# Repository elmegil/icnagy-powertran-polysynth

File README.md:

Forking a powertran polysynth project that appears to have died off before completion

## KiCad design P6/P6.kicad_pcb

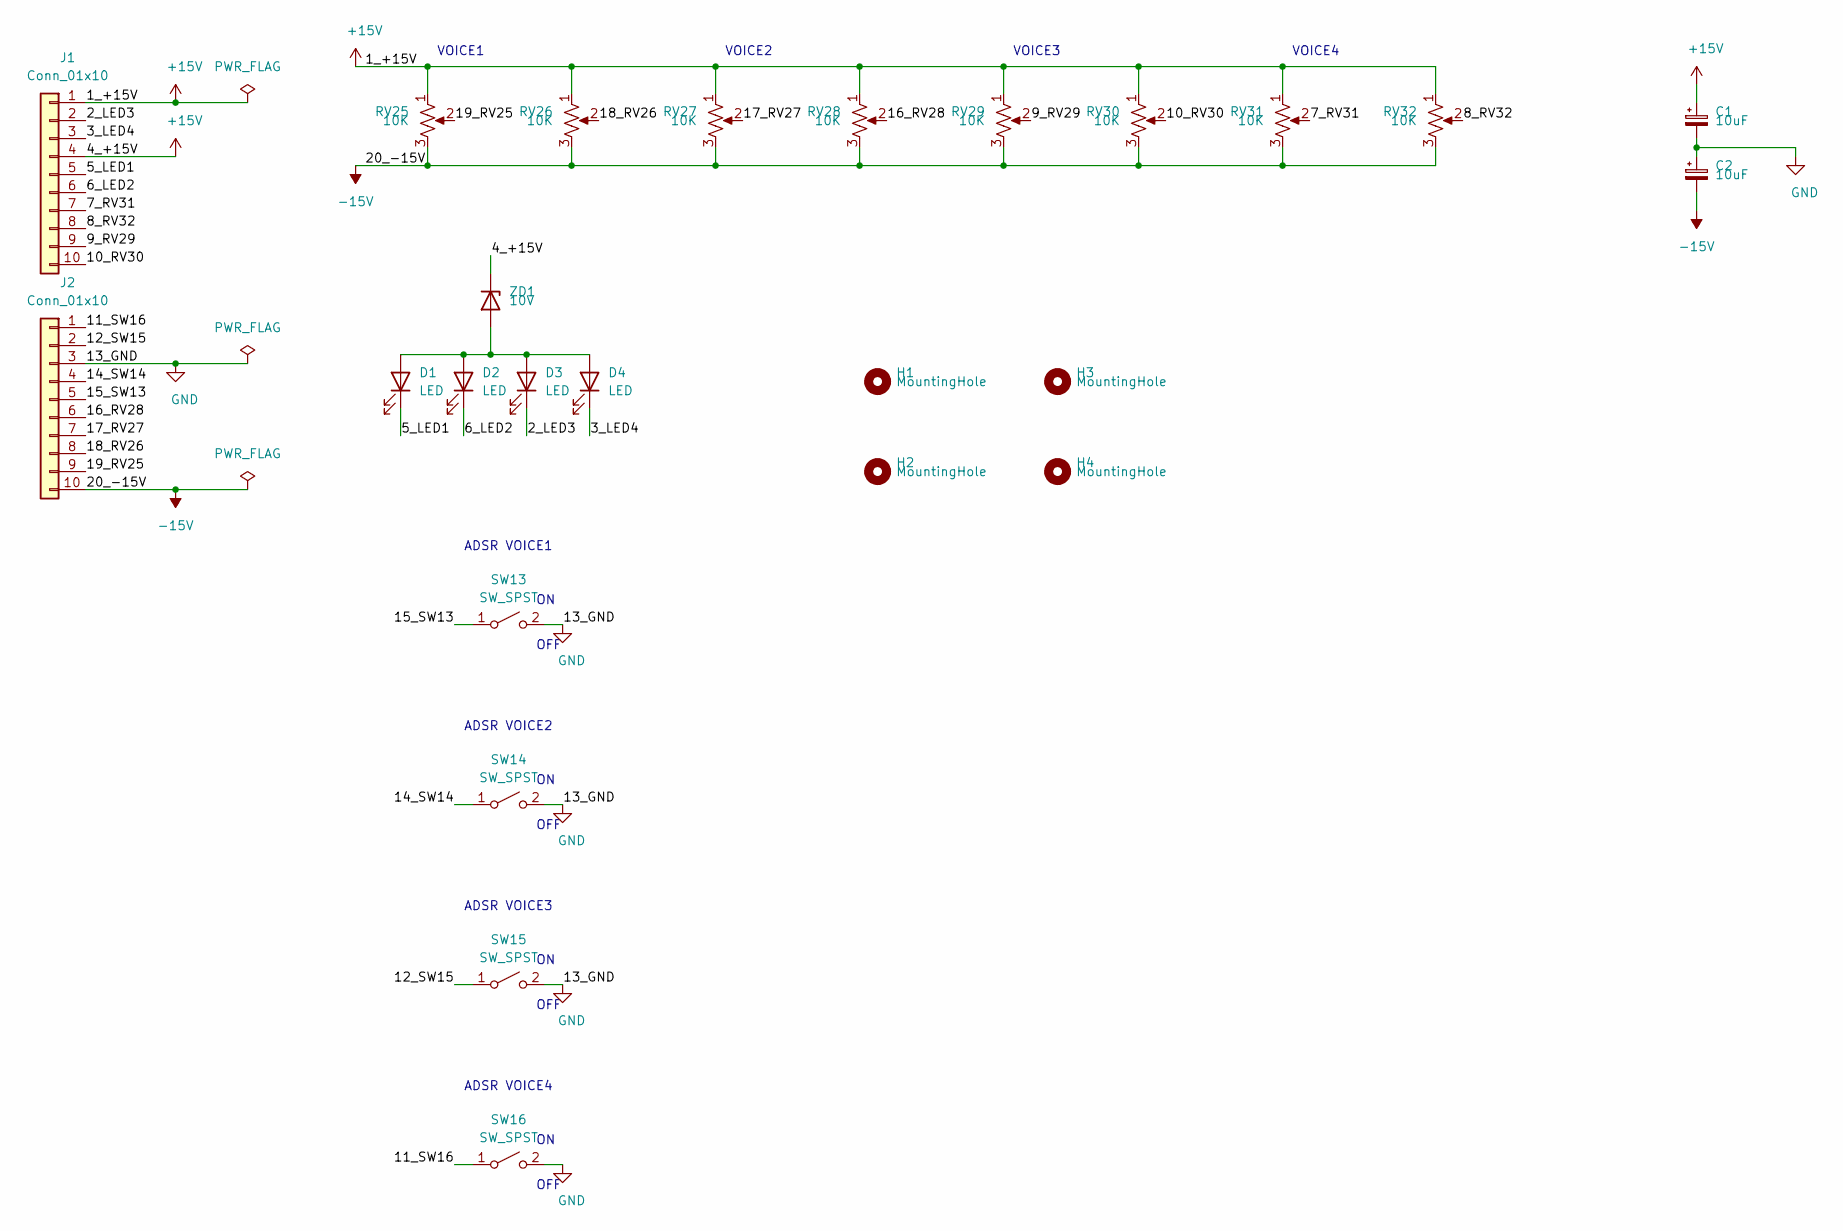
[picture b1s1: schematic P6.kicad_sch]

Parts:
C1, C2: 10uF; CP_Radial_D8.0mm_P3.50mm
D1, D2, D3, D4: LED; LED_D3.0mm
H1, H2, H3, H4: MountingHole; MountingHole_3.2mm_M3_Pad
J1, J2: Conn_01x10; PinSocket_1x10_P2.54mm_Vertical
RV25, RV26, RV27, RV28, RV29, RV30, RV31, RV32: 10K; Potentiometer_Omeg_PC16BU_Vertical
SW13, SW14, SW15, SW16: SW_SPST; SW_Slide_1P2T_CK_OS102011MS2Q
ZD1: 10V; D_A-405_P10.16mm_Horizontal

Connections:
+15V: C1.1, J1.1, J1.4, RV25.1, RV26.1, RV27.1, RV28.1, RV29.1, RV30.1, RV31.1, RV32.1, ZD1.1 (K)
-15V: C2.2, J2.10, RV25.3, RV26.3, RV27.3, RV28.3, RV29.3, RV30.3, RV31.3, RV32.3
/2_LED3: D3.1 (K), J1.2
/3_LED4: D4.1 (K), J1.3
/5_LED1: D1.1 (K), J1.5
/6_LED2: D2.1 (K), J1.6
/7_RV31: J1.7, RV31.2
/8_RV32: J1.8, RV32.2
/9_RV29: J1.9, RV29.2
/10_RV30: J1.10, RV30.2
/11_SW16: J2.1, SW16.1 (A)
/12_SW15: J2.2, SW15.1 (A)
/14_SW14: J2.4, SW14.1 (A)
/15_SW13: J2.5, SW13.1 (A)
/16_RV28: J2.6, RV28.2
/17_RV27: J2.7, RV27.2
/18_RV26: J2.8, RV26.2
/19_RV25: J2.9, RV25.2
GND: C1.2, C2.1, J2.3, SW13.2 (B), SW14.2 (B), SW15.2 (B), SW16.2 (B)
unnamed: D1.2 (A), D2.2 (A), D3.2 (A), D4.2 (A), ZD1.2 (A)

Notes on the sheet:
OFF
VOICE4
VOICE2
VOICE1
ADSR VOICE1
ADSR VOICE2
VOICE3
ADSR VOICE4
ADSR VOICE3

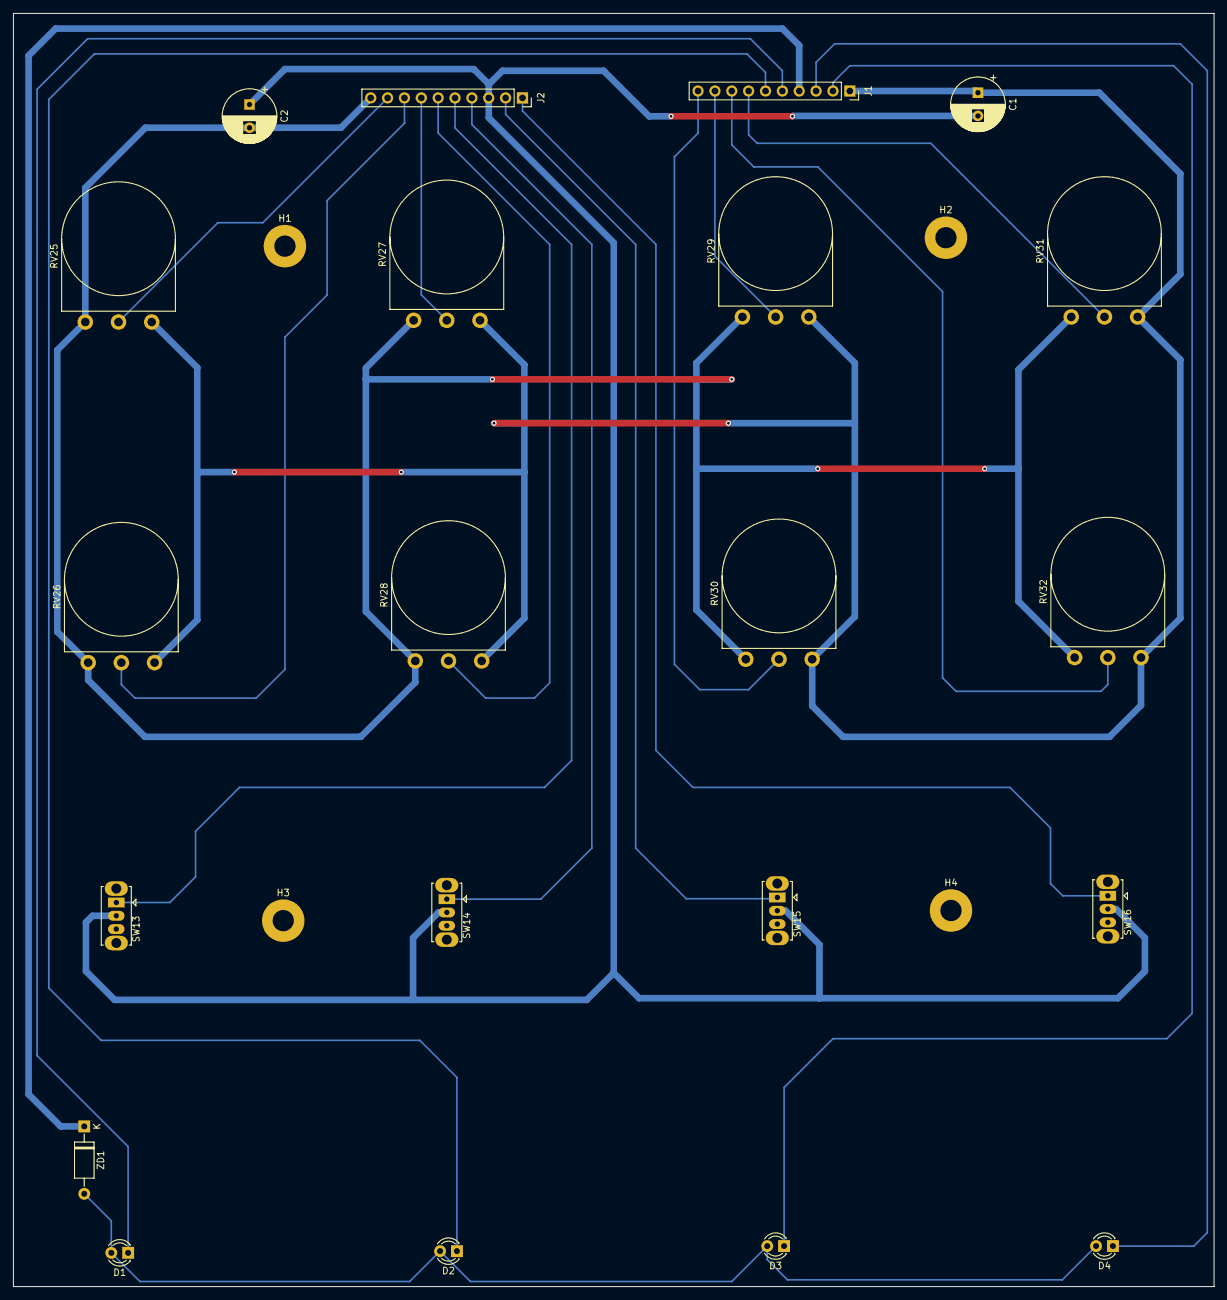
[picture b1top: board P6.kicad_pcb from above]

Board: 2 copper layers, 180.8 x 191.8 mm, 25 parts (0 on the bottom side), 20 nets.

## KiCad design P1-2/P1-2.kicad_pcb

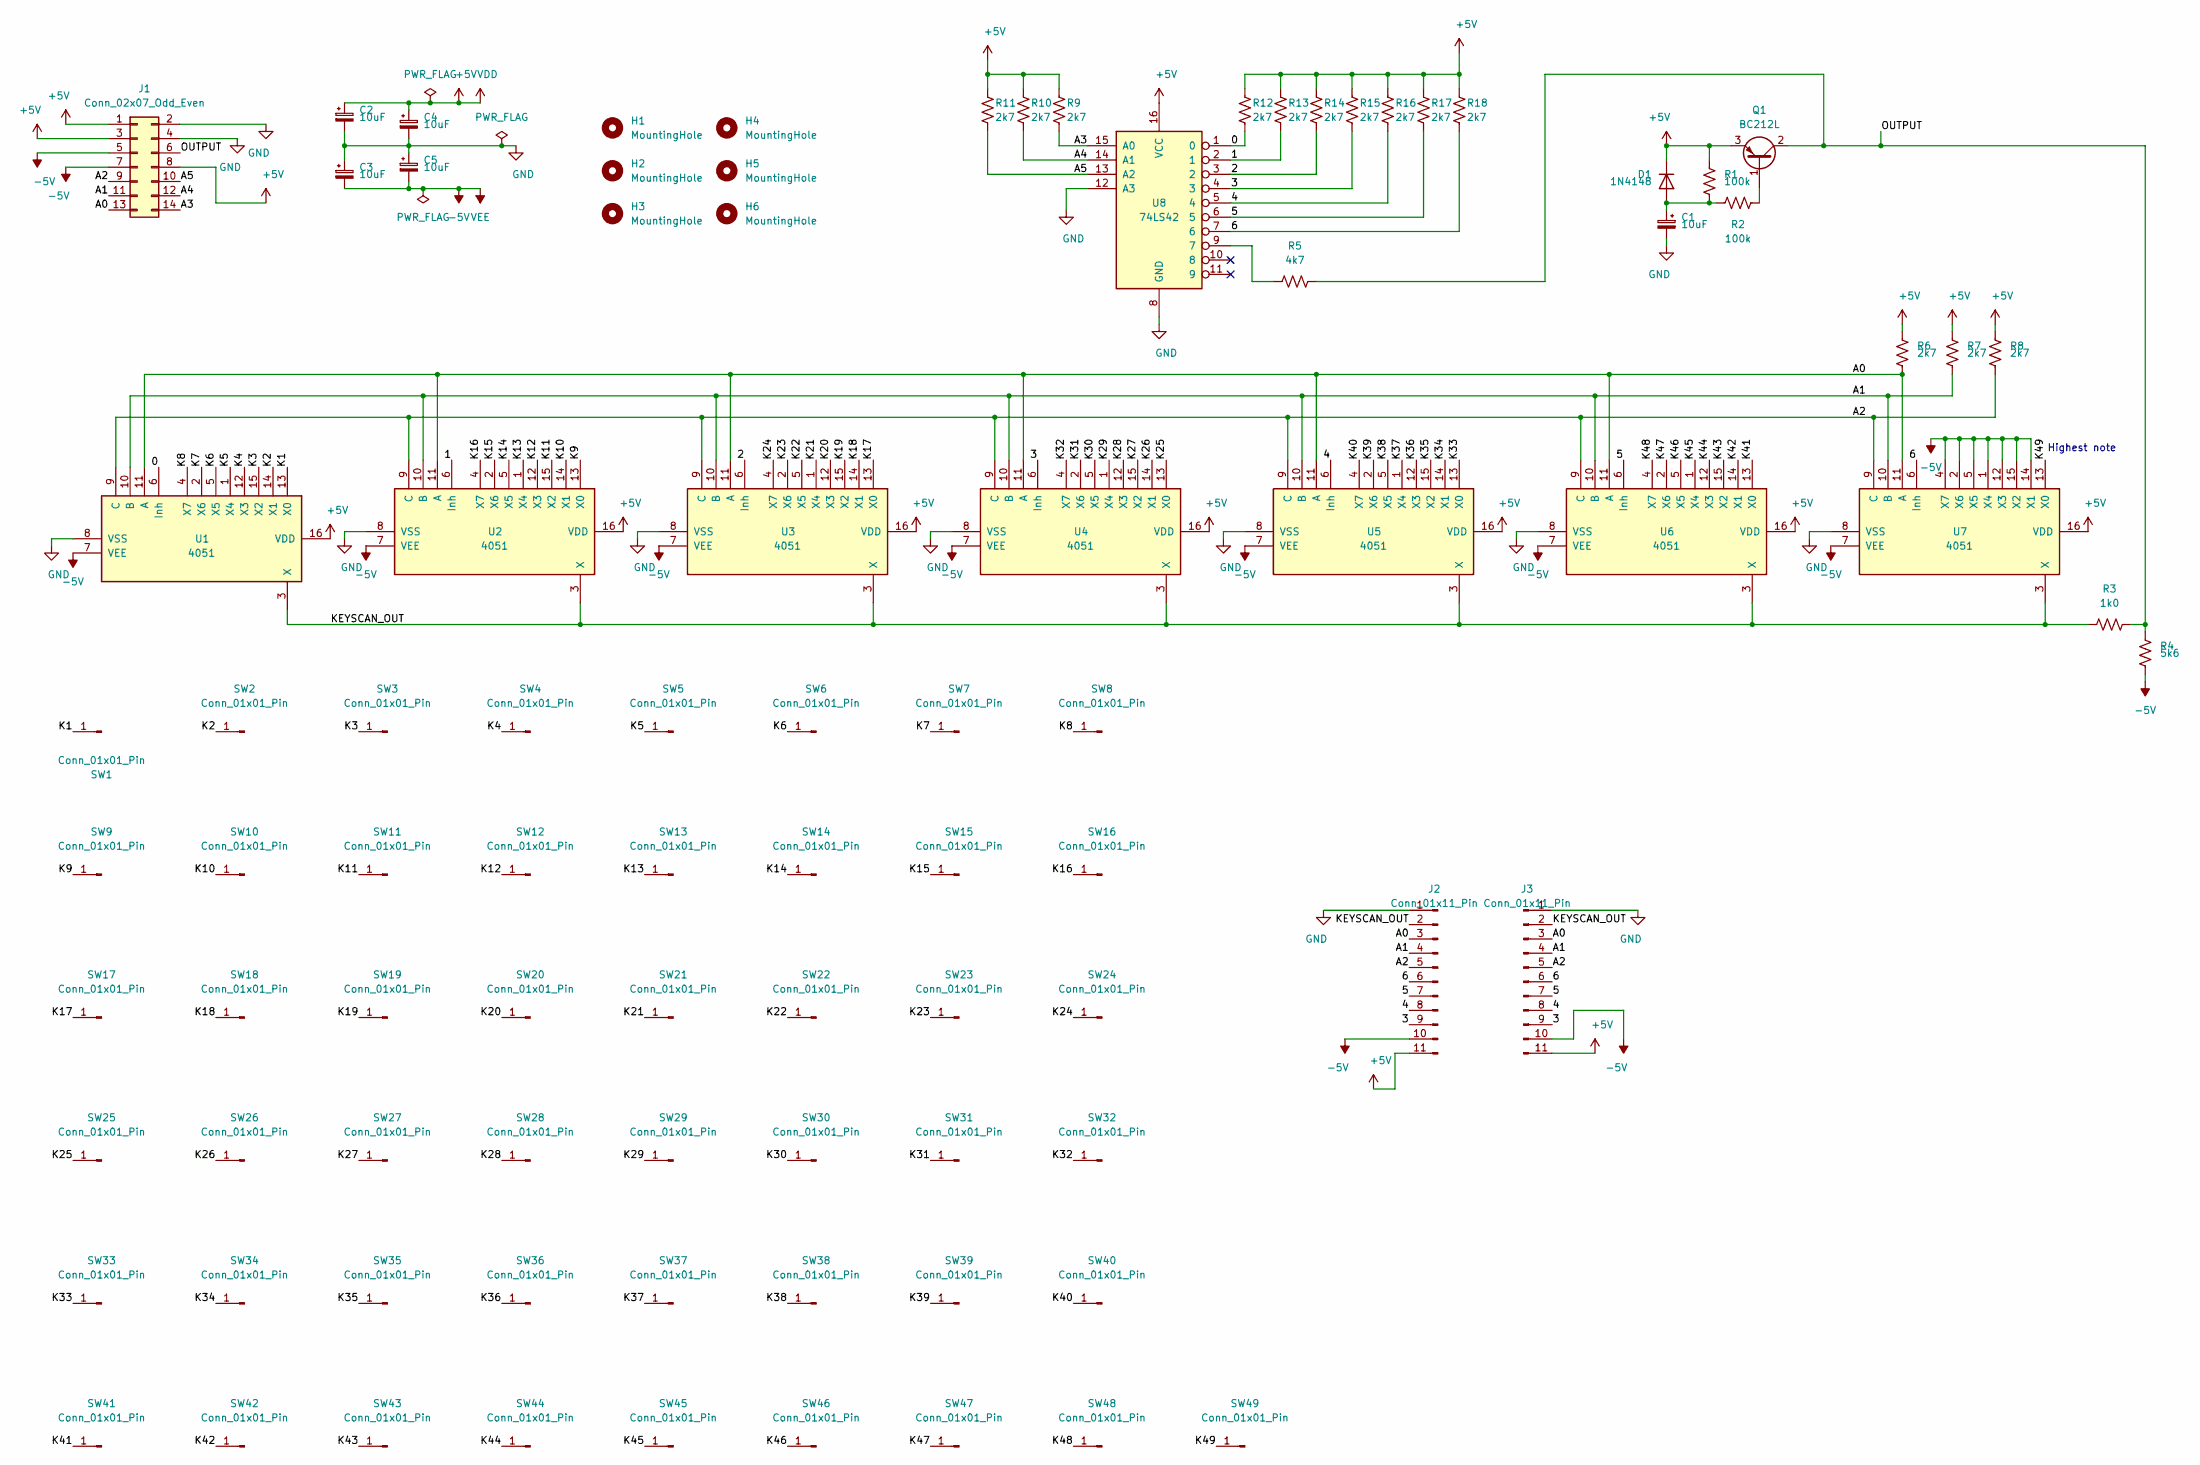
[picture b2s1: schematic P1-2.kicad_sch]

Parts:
C1, C2, C3, C4, C5: 10uF; CP_Radial_D5.0mm_P2.00mm
D1: 1N4148; D_DO-35_SOD27_P7.62mm_Horizontal
H1, H2, H3, H4, H5, H6: MountingHole; MountingHole_3mm_Pad
J1: Conn_02x07_Odd_Even; PinHeader_2x07_P2.54mm_Vertical
J2, J3: Conn_01x11_Pin; PinHeader_1x11_P2.54mm_Vertical
Q1: BC212L; TO-92L_Inline_Wide
R1, R2: 100k; R_Axial_DIN0309_L9.0mm_D3.2mm_P12.70mm_Horizontal
R3: 1k0; R_Axial_DIN0309_L9.0mm_D3.2mm_P12.70mm_Horizontal
R4: 5k6; R_Axial_DIN0309_L9.0mm_D3.2mm_P25.40mm_Horizontal
R5: 4k7; R_Axial_DIN0309_L9.0mm_D3.2mm_P12.70mm_Horizontal
R6, R7, R8, R9, R10, R11, R12: 2k7; R_Axial_DIN0309_L9.0mm_D3.2mm_P12.70mm_Horizontal
R13, R14, R15, R16, R17, R18: 2k7; R_Axial_DIN0309_L9.0mm_D3.2mm_P20.32mm_Horizontal
SW1, SW2, SW3, SW4, SW5, SW6, SW7, SW8, SW9, SW10, SW11, SW12, SW13, SW14, SW15, SW16, SW17, SW18, SW19, SW20, SW21, SW22, SW23, SW24, SW25, SW26, SW27, SW28, SW29, SW30, SW31, SW32, SW33, SW34, SW35, SW36, SW37, SW38, SW39, SW40, SW41, SW42, SW43, SW44, SW45, SW46, SW47, SW48, SW49: Conn_01x01_Pin; Pin_D1.3mm_L11.0mm_LooseFit
U1, U2, U3, U4, U5, U6, U7: 4051; DIP-16_W7.62mm_Socket
U8: 74LS42; DIP-16_W7.62mm_Socket

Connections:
+5V: C2.1, C4.1, D1.1 (K), J1.1, J1.3, J1.8, J2.11, J3.11, Q1.3 (E), R1.2, R6.1, R7.1, R8.1, R9.1, R10.1, R11.1, R12.1, R13.1, R14.1, R15.1, R16.1, R17.1, R18.1, U1.16 (VDD), U2.16 (VDD), U3.16 (VDD), U4.16 (VDD), U5.16 (VDD), U6.16 (VDD), U7.16 (VDD), U8.16 (VCC)
-5V: C3.2, C5.2, J1.5, J1.7, J2.10, J3.10, R4.2, U1.7 (VEE), U2.7 (VEE), U3.7 (VEE), U4.7 (VEE), U5.7 (VEE), U6.7 (VEE), U7.1 (X4), U7.2 (X6), U7.4 (X7), U7.5 (X5), U7.7 (VEE), U7.12 (X3), U7.14 (X1), U7.15 (X2)
/0: R12.2, U1.6 (Inh), U8.1 (0)
/1: R13.2, U2.6 (Inh), U8.2 (1)
/2: R14.2, U3.6 (Inh), U8.3 (2)
/3: J2.9, J3.9, R15.2, U4.6 (Inh), U8.4 (3)
/4: J2.8, J3.8, R16.2, U5.6 (Inh), U8.5 (4)
/5: J2.7, J3.7, R17.2, U6.6 (Inh), U8.6 (5)
/6: J2.6, J3.6, R18.2, U7.6 (Inh), U8.7 (6)
/A0: J1.13, J2.3, J3.3, R6.2, U1.11 (A), U2.11 (A), U3.11 (A), U4.11 (A), U5.11 (A), U6.11 (A), U7.11 (A)
/A1: J1.11, J2.4, J3.4, R7.2, U1.10 (B), U2.10 (B), U3.10 (B), U4.10 (B), U5.10 (B), U6.10 (B), U7.10 (B)
/A2: J1.9, J2.5, J3.5, R8.2, U1.9 (C), U2.9 (C), U3.9 (C), U4.9 (C), U5.9 (C), U6.9 (C), U7.9 (C)
/A3: J1.14, R9.2, U8.15 (A0)
/A4: J1.12, R10.2, U8.14 (A1)
/A5: J1.10, R11.2, U8.13 (A2)
/K1: SW1.1, U1.13 (X0)
/K2: SW2.1, U1.14 (X1)
/K3: SW3.1, U1.15 (X2)
/K4: SW4.1, U1.12 (X3)
/K5: SW5.1, U1.1 (X4)
/K6: SW6.1, U1.5 (X5)
/K7: SW7.1, U1.2 (X6)
/K8: SW8.1, U1.4 (X7)
/K9: SW9.1, U2.13 (X0)
/K10: SW10.1, U2.14 (X1)
/K11: SW11.1, U2.15 (X2)
/K12: SW12.1, U2.12 (X3)
/K13: SW13.1, U2.1 (X4)
/K14: SW14.1, U2.5 (X5)
/K15: SW15.1, U2.2 (X6)
/K16: SW16.1, U2.4 (X7)
/K17: SW17.1, U3.13 (X0)
/K18: SW18.1, U3.14 (X1)
/K19: SW19.1, U3.15 (X2)
/K20: SW20.1, U3.12 (X3)
/K21: SW21.1, U3.1 (X4)
/K22: SW22.1, U3.5 (X5)
/K23: SW23.1, U3.2 (X6)
/K24: SW24.1, U3.4 (X7)
/K25: SW25.1, U4.13 (X0)
/K26: SW26.1, U4.14 (X1)
/K27: SW27.1, U4.15 (X2)
/K28: SW28.1, U4.12 (X3)
/K29: SW29.1, U4.1 (X4)
/K30: SW30.1, U4.5 (X5)
/K31: SW31.1, U4.2 (X6)
/K32: SW32.1, U4.4 (X7)
/K33: SW33.1, U5.13 (X0)
/K34: SW34.1, U5.14 (X1)
/K35: SW35.1, U5.15 (X2)
/K36: SW36.1, U5.12 (X3)
/K37: SW37.1, U5.1 (X4)
/K38: SW38.1, U5.5 (X5)
/K39: SW39.1, U5.2 (X6)
/K40: SW40.1, U5.4 (X7)
/K41: SW41.1, U6.13 (X0)
/K42: SW42.1, U6.14 (X1)
/K43: SW43.1, U6.15 (X2)
/K44: SW44.1, U6.12 (X3)
/K45: SW45.1, U6.1 (X4)
/K46: SW46.1, U6.5 (X5)
/K47: SW47.1, U6.2 (X6)
/K48: SW48.1, U6.4 (X7)
/K49: SW49.1, U7.13 (X0)
/KEYSCAN_OUT: J2.2, J3.2, R3.2, U1.3 (X), U2.3 (X), U3.3 (X), U4.3 (X), U5.3 (X), U6.3 (X), U7.3 (X)
/OUTPUT: J1.6, Q1.2 (C), R3.1, R4.1, R5.1
GND: C1.2, C2.2, C3.1, C4.2, C5.1, J1.2, J1.4, J2.1, J3.1, U1.8 (VSS), U2.8 (VSS), U3.8 (VSS), U4.8 (VSS), U5.8 (VSS), U6.8 (VSS), U7.8 (VSS), U8.8 (GND), U8.12 (A3)
unnamed: C1.1, D1.2 (A), R1.1, R2.1
unnamed: Q1.1 (B), R2.2
unnamed: R5.2, U8.9 (7)

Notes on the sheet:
Highest note

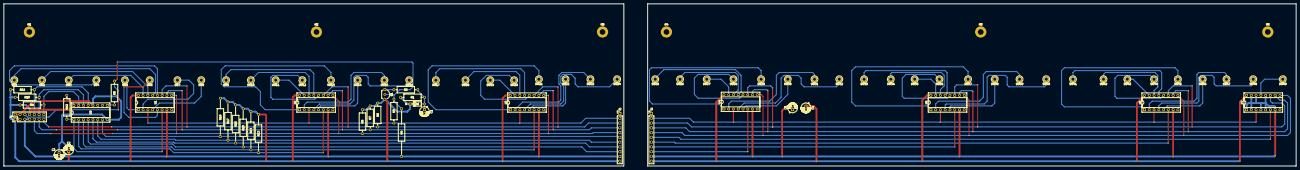
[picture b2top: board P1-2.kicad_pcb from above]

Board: 2 copper layers, 688.3 x 86.4 mm, 91 parts (0 on the bottom side), 70 nets.

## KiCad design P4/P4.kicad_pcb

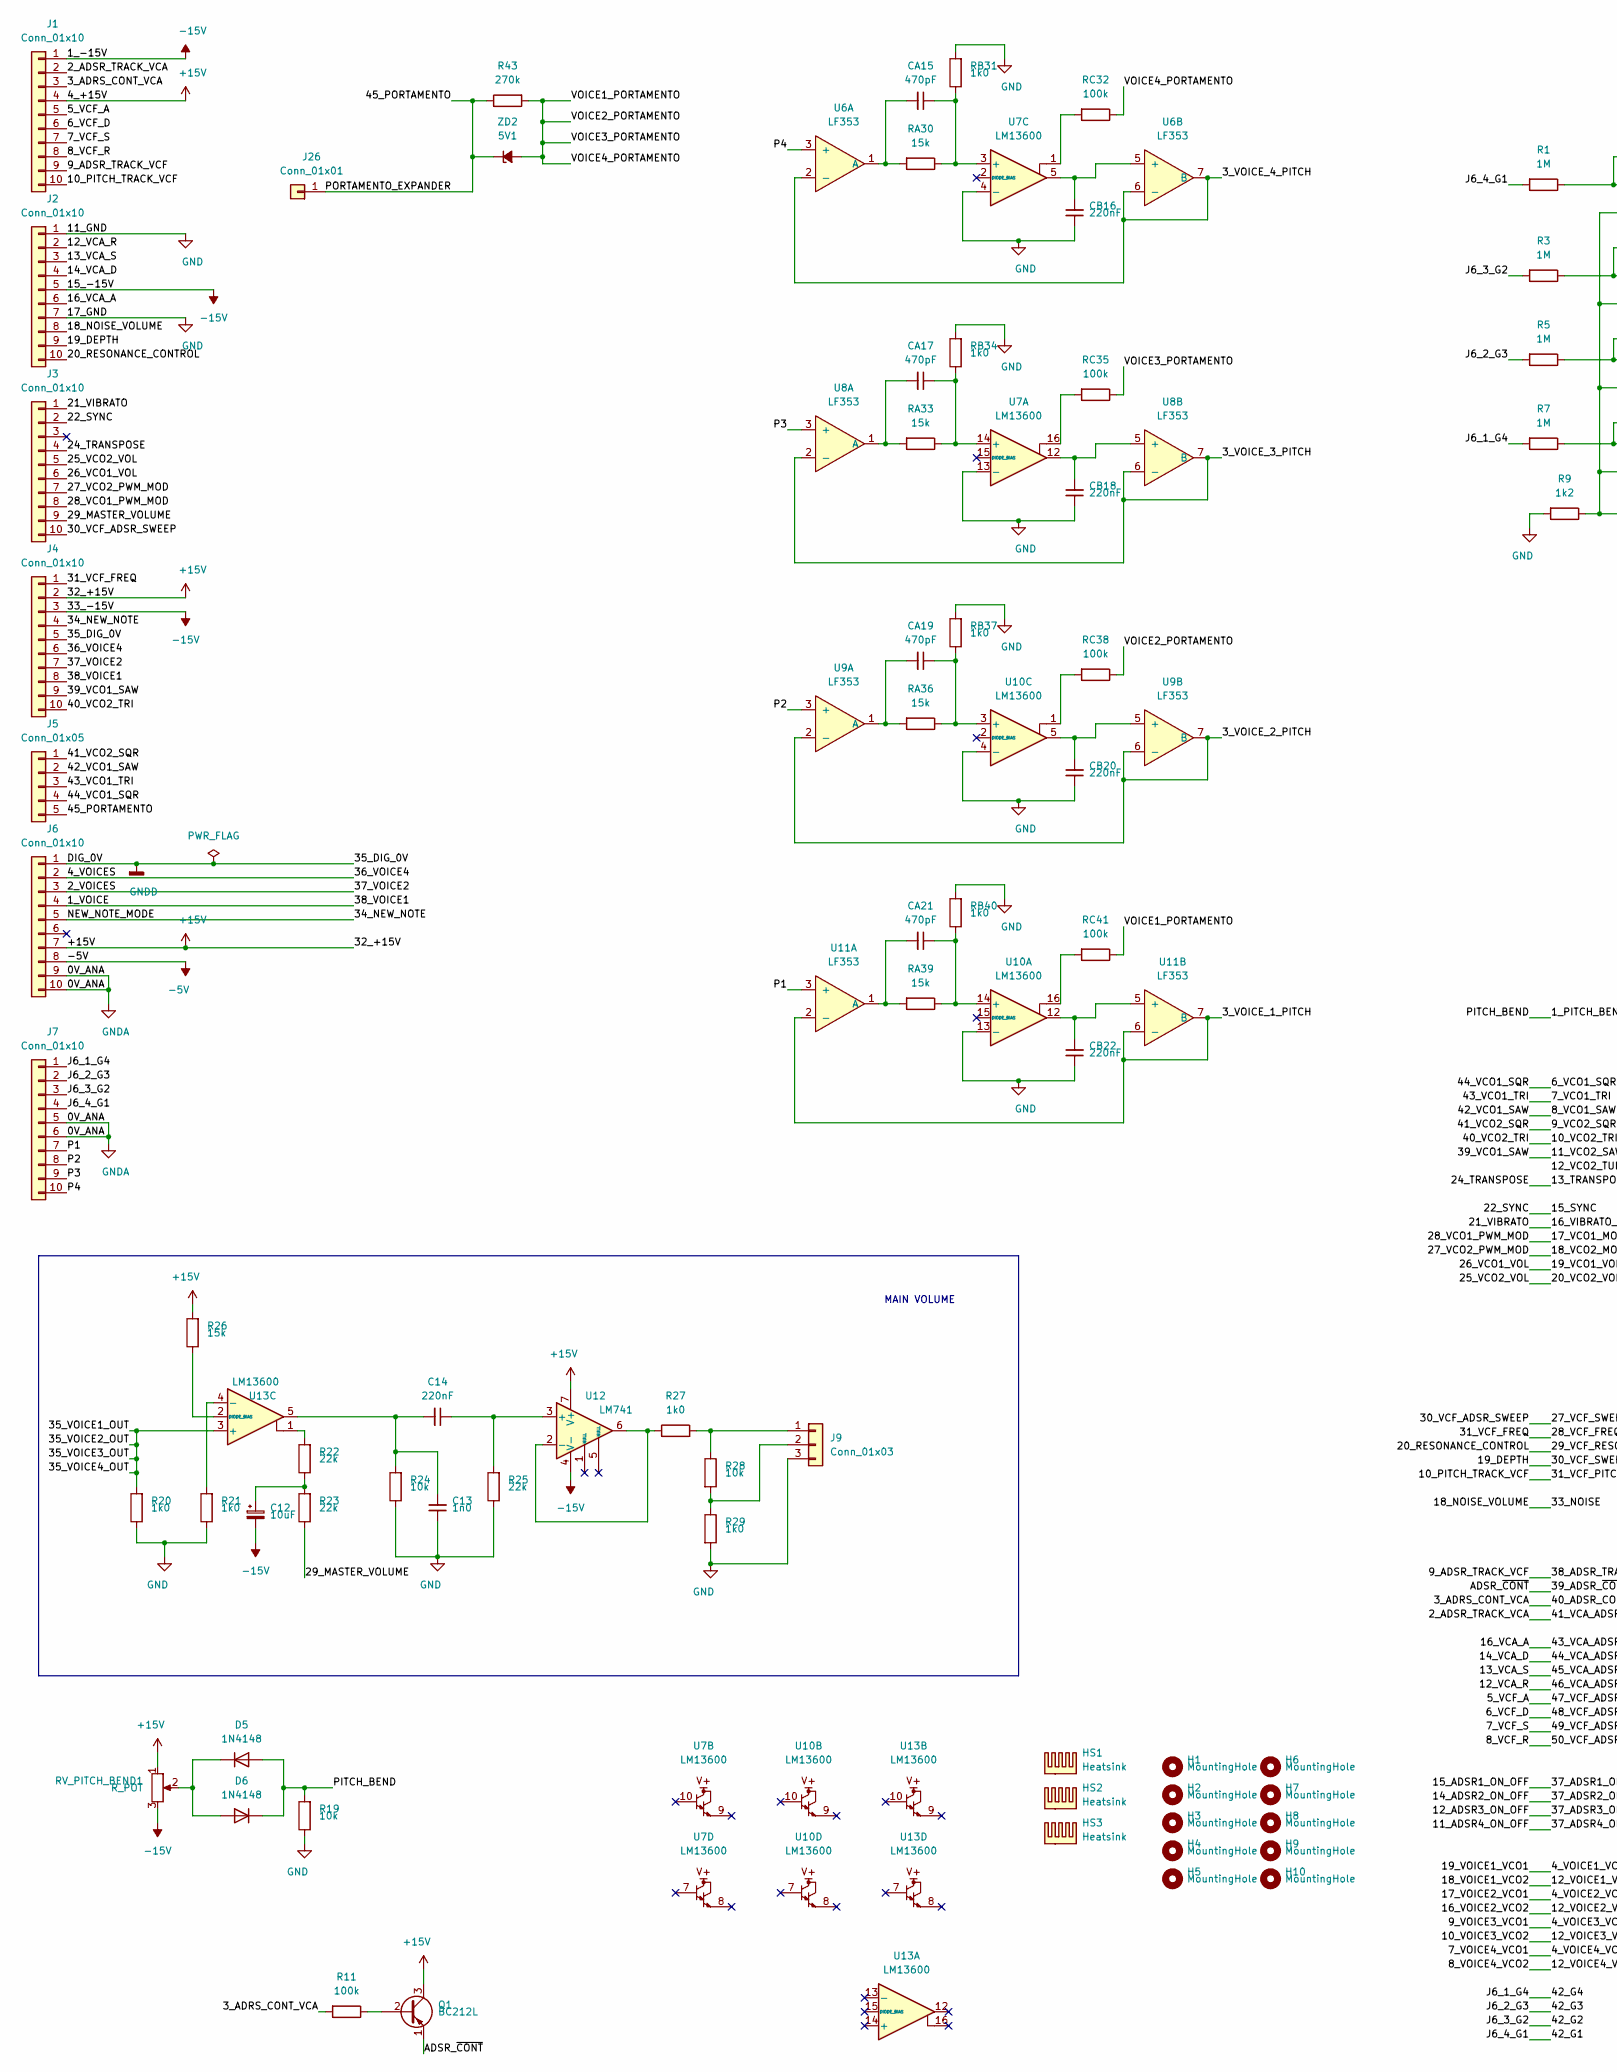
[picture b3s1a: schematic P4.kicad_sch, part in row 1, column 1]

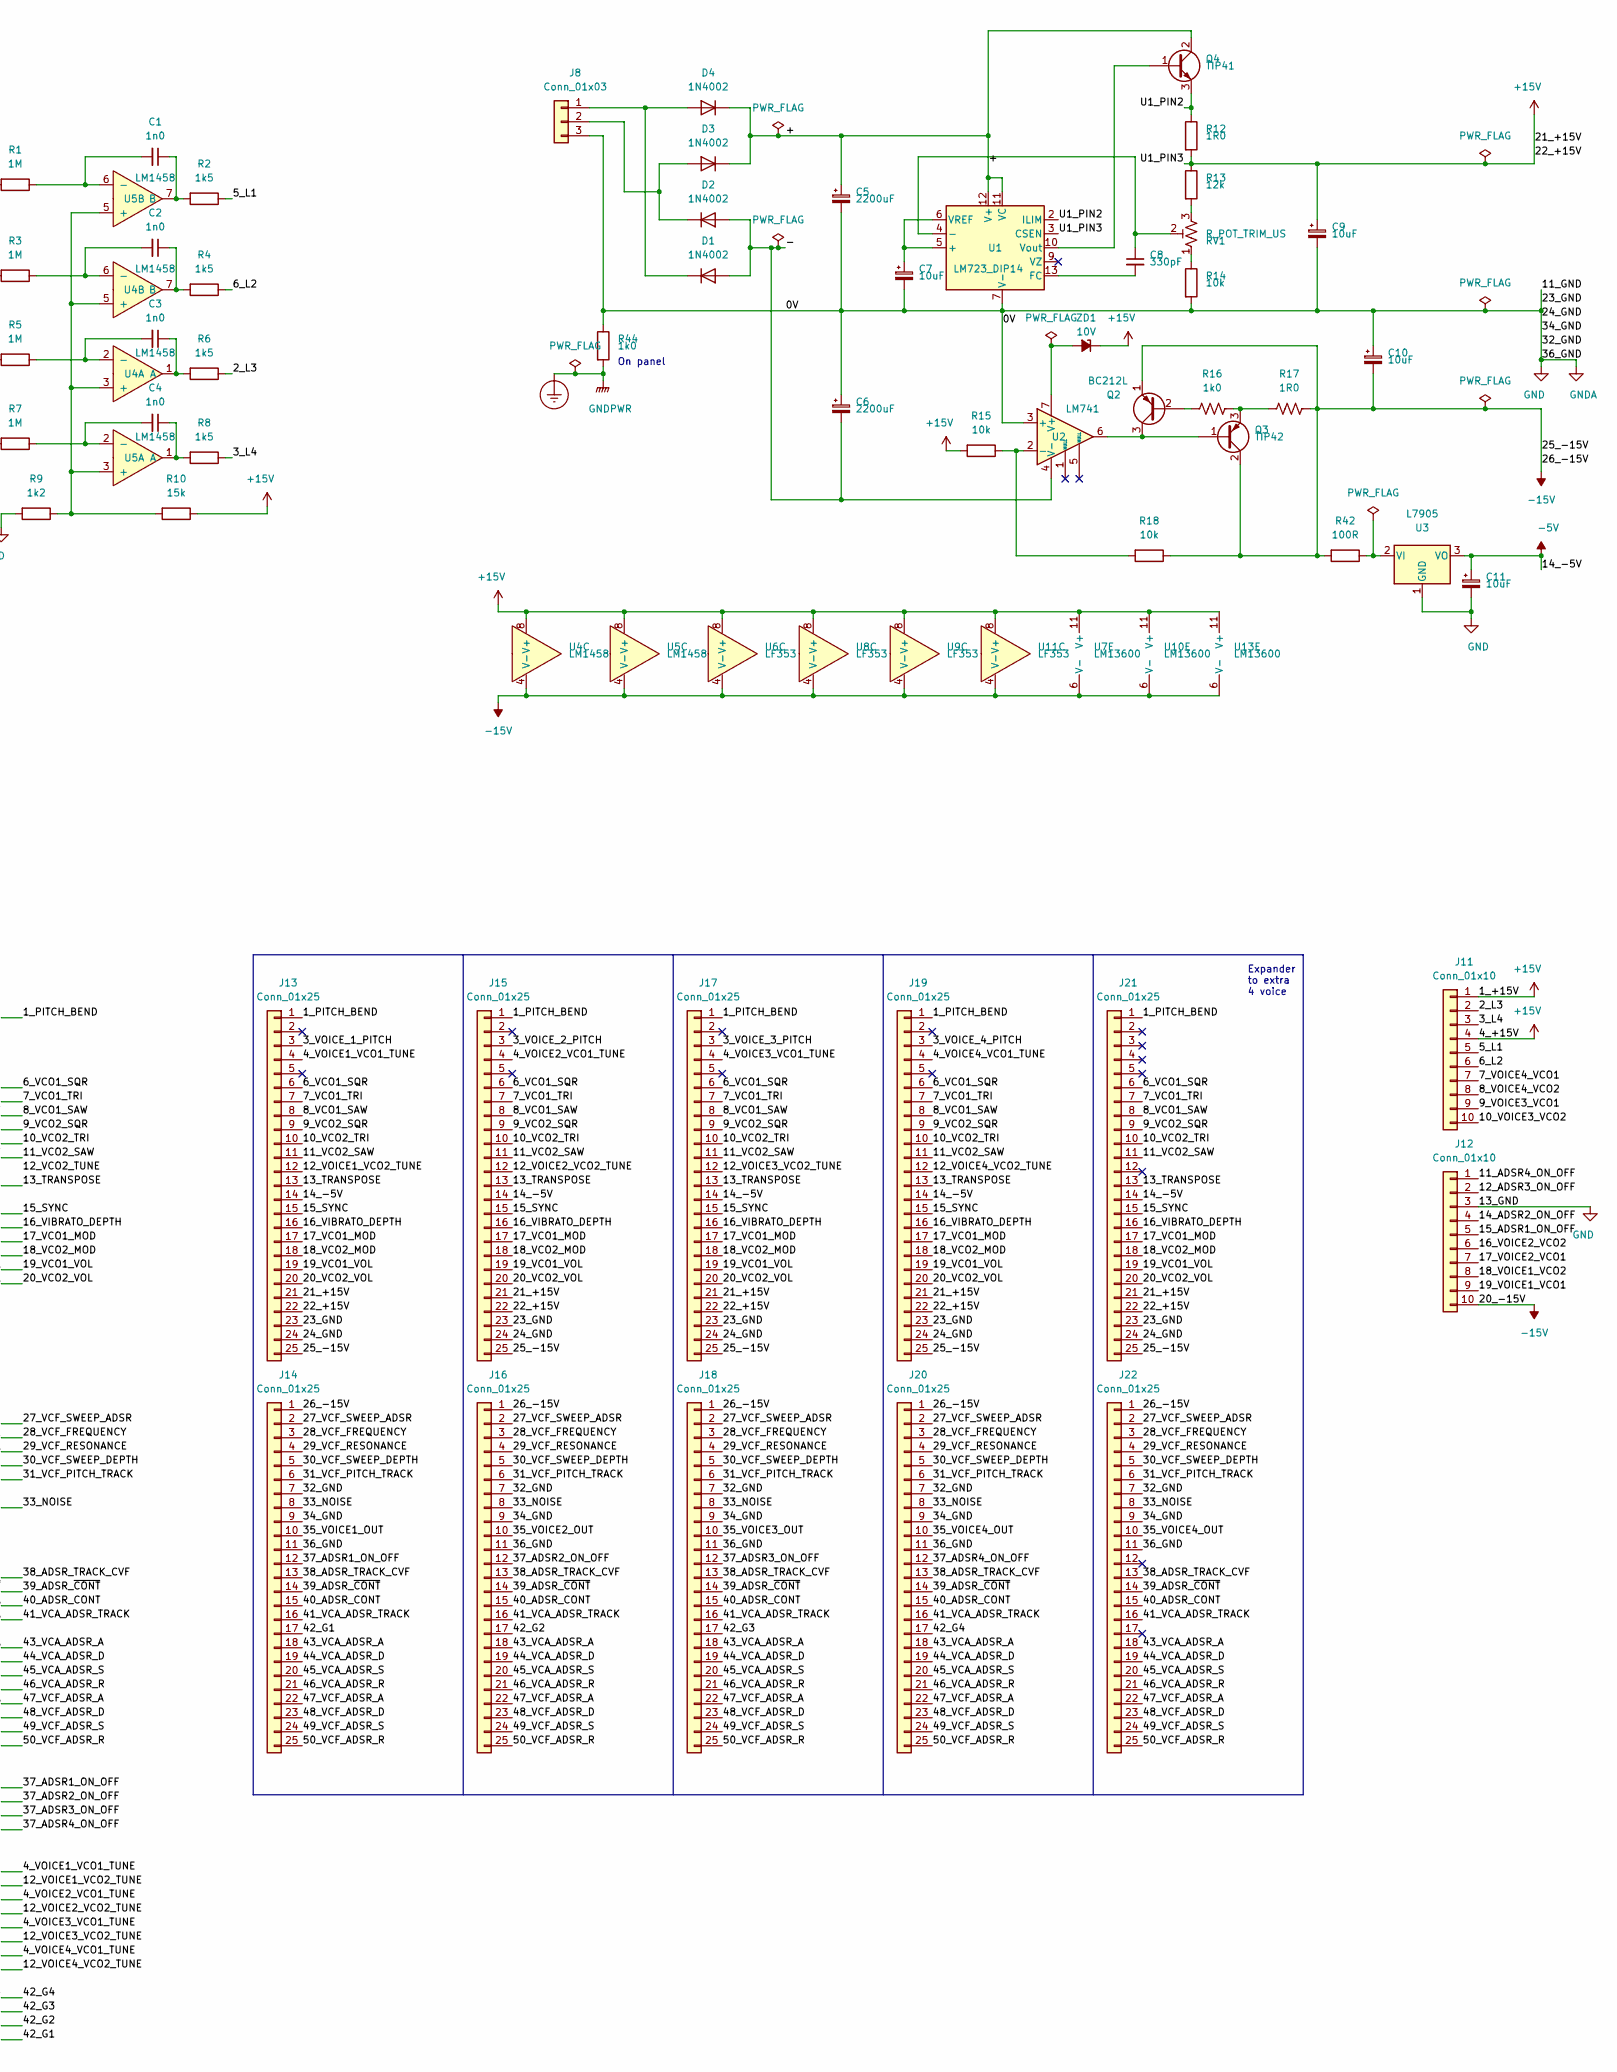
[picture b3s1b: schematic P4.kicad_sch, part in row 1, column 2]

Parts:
C1, C2, C3, C4, C13: 1n0; C_Disc_D5.0mm_W2.5mm_P5.00mm
C5, C6: 2200uF; CP_Axial_L20.0mm_D13.0mm_P26.00mm_Horizontal
C7, C9, C10, C11, C12: 10uF; CP_Radial_D6.3mm_P2.50mm
C8: 330pF; C_Disc_D5.0mm_W2.5mm_P5.00mm
C14: 220nF; C_Disc_D5.0mm_W2.5mm_P5.00mm
CA15, CA17, CA19, CA21: 470pF; C_Disc_D5.0mm_W2.5mm_P5.00mm
CB16, CB18, CB20, CB22: 220nF; C_Disc_D5.0mm_W2.5mm_P5.00mm
D1, D2, D3, D4: 1N4002; D_DO-41_SOD81_P10.16mm_Horizontal
D5, D6: 1N4148; D_DO-15_P12.70mm_Horizontal
H1, H2, H3, H4, H5, H6, H7, H8, H9, H10: MountingHole; MountingHole_3.2mm_M3_Pad
HS1, HS2, HS3: Heatsink; Heatsink_Stonecold_HS-132_32x14mm_2xFixation1.5mm
J1, J2, J3, J4, J6, J7, J11, J12: Conn_01x10; PinHeader_1x10_P2.54mm_Vertical
J5: Conn_01x05; PinHeader_1x05_P2.54mm_Vertical
J8, J9: Conn_01x03; PinHeader_1x03_P2.54mm_Vertical
J13, J14, J15, J16, J17, J18, J19, J20, J21, J22: Conn_01x25; PinSocket_1x25_P2.54mm_Vertical
J26: Conn_01x01; SolderWire-1.5sqmm_1x01_D1.7mm_OD3.9mm
Q1, Q2: BC212L; TO-92L_Wide
Q3: TIP42; TO-220-3_Vertical
Q4: TIP41; TO-220-3_Vertical
R1, R3, R5, R7: 1M; R_Axial_DIN0207_L6.3mm_D2.5mm_P7.62mm_Horizontal
R2, R4, R6, R8: 1k5; R_Axial_DIN0207_L6.3mm_D2.5mm_P7.62mm_Horizontal
R9: 1k2; R_Axial_DIN0207_L6.3mm_D2.5mm_P7.62mm_Horizontal
R10, R26: 15k; R_Axial_DIN0207_L6.3mm_D2.5mm_P7.62mm_Horizontal
R11: 100k; R_Axial_DIN0207_L6.3mm_D2.5mm_P7.62mm_Horizontal
R12, R17: 1R0; R_Axial_DIN0207_L6.3mm_D2.5mm_P7.62mm_Horizontal
R13: 12k; R_Axial_DIN0207_L6.3mm_D2.5mm_P7.62mm_Horizontal
R14, R15, R18, R19, R24, R28: 10k; R_Axial_DIN0207_L6.3mm_D2.5mm_P7.62mm_Horizontal
R16, R20, R21, R27, R29, R44: 1k0; R_Axial_DIN0207_L6.3mm_D2.5mm_P7.62mm_Horizontal
R22, R23, R25: 22k; R_Axial_DIN0207_L6.3mm_D2.5mm_P7.62mm_Horizontal
R42: 100R; R_Axial_DIN0207_L6.3mm_D2.5mm_P7.62mm_Horizontal
R43: 270k; R_Axial_DIN0207_L6.3mm_D2.5mm_P7.62mm_Horizontal
RA30, RA33, RA36, RA39: 15k; R_Axial_DIN0207_L6.3mm_D2.5mm_P7.62mm_Horizontal
RB31, RB34, RB37, RB40: 1k0; R_Axial_DIN0207_L6.3mm_D2.5mm_P7.62mm_Horizontal
RC32, RC35, RC38, RC41: 100k; R_Axial_DIN0207_L6.3mm_D2.5mm_P7.62mm_Horizontal
RV1: R_POT_TRIM_US; Potentiometer_Bourns_3296Y_Vertical
RV_PITCH_BEND1: R_POT; PinHeader_1x03_P2.54mm_Vertical
U1: LM723_DIP14; DIP-14_W7.62mm
U2, U12: LM741; DIP-8_W7.62mm_Socket_LongPads
U3: L7905; TO-220-3_Vertical
U4, U5: LM1458; DIP-8_W7.62mm_Socket_LongPads
U6, U8, U9, U11: LF353; DIP-8_W7.62mm_Socket_LongPads
U7, U10, U13: LM13600; DIP-16_W7.62mm_Socket_LongPads
ZD1: 10V; D_DO-15_P10.16mm_Horizontal
ZD2: 5V1; D_DO-15_P10.16mm_Horizontal

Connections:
+15V: C9.1, J1.4, J4.2, J6.7, J11.1, J11.4, J13.21, J13.22, J15.21, J15.22, J17.21, J17.22, J19.21, J19.22, J21.21, J21.22, Q1.3 (C), R10.1, R12.2, R13.1, R15.2, R26.2, RV_PITCH_BEND1.1, U1.3 (CSEN), U4.8 (V+), U5.8 (V+), U6.8 (V+), U7.11 (V+), U8.8 (V+), U9.8 (V+), U10.11 (V+), U11.8 (V+), U12.7 (V+), U13.11 (V+), ZD1.1 (K)
-5V: C11.1, J6.8, J13.14, J15.14, J17.14, J19.14, J21.14, U3.3 (VO)
-15V: C10.2, C12.2, J1.1, J2.5, J4.3, J12.10, J13.25, J14.1, J15.25, J16.1, J17.25, J18.1, J19.25, J20.1, J21.25, J22.1, Q2.1 (E), Q3.2 (C), R17.1, R18.1, R42.2, RV_PITCH_BEND1.3, U4.4 (V-), U5.4 (V-), U6.4 (V-), U7.6 (V-), U8.4 (V-), U9.4 (V-), U10.6 (V-), U11.4 (V-), U12.4 (V-), U13.6 (V-)
/1_PITCH_BEND: D5.2 (A), D6.1 (K), J13.1, J15.1, J17.1, J19.1, J21.1, R19.2
/1_VOICE: J4.8, J6.4
/2_ADSR_TRACK_VCA: J1.2, J14.16, J16.16, J18.16, J20.16, J22.16
/2_L3: J11.2, R6.1
/2_VOICES: J4.7, J6.3
/3_ADRS_CONT_VCA: J1.3, J14.15, J16.15, J18.15, J20.15, J22.15, R11.2
/3_L4: J11.3, R8.1
/3_VOICE_1_PITCH: J13.3, U11.2 (-), U11.6 (-), U11.7 (B)
/3_VOICE_2_PITCH: J15.3, U9.2 (-), U9.6 (-), U9.7 (B)
/3_VOICE_3_PITCH: J17.3, U8.2 (-), U8.6 (-), U8.7 (B)
/3_VOICE_4_PITCH: J19.3, U6.2 (-), U6.6 (-), U6.7 (B)
/4_VOICE3_VCO1_TUNE: J11.9, J17.4
/4_VOICE4_VCO1_TUNE: J11.7, J19.4
/5_L1: J11.5, R2.1
/6_L2: J11.6, R4.1
/10_PITCH_TRACK_VCF: J1.10, J14.6, J16.6, J18.6, J20.6, J22.6
/10_VCO2_TRI: J4.10, J13.10, J15.10, J17.10, J19.10, J21.10
/10_VOICE3_VCO2: J11.10, J17.12
/11_ADSR4_ON_OFF: J12.1, J20.12
/11_VCO2_SAW: J4.9, J13.11, J15.11, J17.11, J19.11, J21.11
/12_ADSR3_ON_OFF: J12.2, J18.12
/12_VCA_R: J2.2, J14.21, J16.21, J18.21, J20.21, J22.21
/12_VOICE1_VCO2_TUNE: J12.8, J13.12
/12_VOICE2_VCO2_TUNE: J12.6, J15.12
/12_VOICE4_VCO2_TUNE: J11.8, J19.12
/13_TRANSPOSE: J3.4, J13.13, J15.13, J17.13, J19.13, J21.13
/13_VCA_S: J2.3, J14.20, J16.20, J18.20, J20.20, J22.20
/14_ADSR2_ON_OFF: J12.4, J16.12
/14_VCA_D: J2.4, J14.19, J16.19, J18.19, J20.19, J22.19
/15_ADSR1_ON_OFF: J12.5, J14.12
/15_SYNC: J3.2, J13.15, J15.15, J17.15, J19.15, J21.15
/16_VCA_A: J2.6, J14.18, J16.18, J18.18, J20.18, J22.18
/16_VIBRATO_DEPTH: J3.1, J13.16, J15.16, J17.16, J19.16, J21.16
/17_VCO1_MOD: J3.8, J13.17, J15.17, J17.17, J19.17, J21.17
/17_VOICE2_VCO1: J12.7, J15.4
/18_NOISE_VOLUME: J2.8, J14.8, J16.8, J18.8, J20.8, J22.8
/18_VCO2_MOD: J3.7, J13.18, J15.18, J17.18, J19.18, J21.18
/19_DEPTH: J2.9, J14.5, J16.5, J18.5, J20.5, J22.5
/19_VCO1_VOL: J3.6, J13.19, J15.19, J17.19, J19.19, J21.19
/19_VOICE1_VCO1: J12.9, J13.4
/20_RESONANCE_CONTROL: J2.10, J14.4, J16.4, J18.4, J20.4, J22.4
/20_VCO2_VOL: J3.5, J13.20, J15.20, J17.20, J19.20, J21.20
/27_VCF_SWEEP_ADSR: J3.10, J14.2, J16.2, J18.2, J20.2, J22.2
/28_VCF_FREQUENCY: J4.1, J14.3, J16.3, J18.3, J20.3, J22.3
/29_MASTER_VOLUME: J3.9, R23.1
/34_NEW_NOTE: J4.4, J6.5
/35_VOICE1_OUT: J14.10, J16.10, J18.10, J20.10, J22.10, R20.2, U13.3 (+)
/36_VOICE4: J4.6, J6.2
/38_ADSR_TRACK_CVF: J1.9, J14.13, J16.13, J18.13, J20.13, J22.13
/39_ADSR_~CONT: J14.14, J16.14, J18.14, J20.14, J22.14, Q1.1 (E)
/41_VCO2_SQR: J5.1, J13.9, J15.9, J17.9, J19.9, J21.9
/42_G1: J7.4, J14.17, R1.2
/42_G2: J7.3, J16.17, R3.2
/42_G3: J7.2, J18.17, R5.2
/42_G4: J7.1, J20.17, R7.2
/42_VCO1_SAW: J5.2, J13.8, J15.8, J17.8, J19.8, J21.8
/43_VCO1_TRI: J5.3, J13.7, J15.7, J17.7, J19.7, J21.7
/44_VCO1_SQR: J5.4, J13.6, J15.6, J17.6, J19.6, J21.6
/45_PORTAMENTO: J5.5, J26.1, R43.1, ZD2.1 (K)
/47_VCF_ADSR_A: J1.5, J14.22, J16.22, J18.22, J20.22, J22.22
/48_VCF_ADSR_D: J1.6, J14.23, J16.23, J18.23, J20.23, J22.23
/49_VCF_ADSR_S: J1.7, J14.24, J16.24, J18.24, J20.24, J22.24
/50_VCF_ADSR_R: J1.8, J14.25, J16.25, J18.25, J20.25, J22.25
/+: C5.1, D3.1 (K), D4.1 (K), Q4.2 (C), U1.11 (VC), U1.12 (V+)
/-: C6.2, D1.2 (A), D2.2 (A), U2.4 (V-)
/P1: J7.7, U11.3 (+)
/P2: J7.8, U9.3 (+)
/P3: J7.9, U8.3 (+)
/P4: J7.10, U6.3 (+)
/U1_PIN2: Q4.3 (E), R12.1, U1.2 (ILIM)
/VOICE1_PORTAMENTO: R43.2, RC32.1, RC35.1, RC38.1, RC41.1, ZD2.2 (A)
GND: C5.2, C6.1, C7.2, C9.2, C10.1, C11.2, C13.1, CB16.1, CB18.1, CB20.1, CB22.1, J2.1, J2.7, J6.9, J6.10, J7.5, J7.6, J8.3, J9.3, J12.3, J13.23, J13.24, J14.7, J14.9, J14.11, J15.23, J15.24, J16.7, J16.9, J16.11, J17.23, J17.24, J18.7, J18.9, J18.11, J19.23, J19.24, J20.7, J20.9, J20.11, J21.23, J21.24, J22.7, J22.9, J22.11, R9.2, R14.2, R19.1, R20.1, R21.1, R24.1, R25.1, R29.2, R44.1, RB31.2, RB34.2, RB37.2, RB40.2, U1.7 (V-), U2.3 (+), U3.1 (GND), U7.4 (-), U7.13 (-), U10.4 (-), U10.13 (-)
GNDD: J4.5, J6.1
unnamed: C1.1, R2.2, U5.7 (B)
unnamed: C1.2, R1.1, U5.6 (-)
unnamed: C2.1, R4.2, U4.7 (B)
unnamed: C2.2, R3.1, U4.6 (-)
unnamed: C3.1, R6.2, U4.1 (A)
unnamed: C3.2, R5.1, U4.2 (-)
unnamed: C4.1, R8.2, U5.1 (A)
unnamed: C4.2, R7.1, U5.2 (-)
unnamed: C7.1, U1.5 (+), U1.6 (VREF)
unnamed: C8.1, RV1.2, U1.4 (-)
unnamed: C8.2, U1.13 (FC)
unnamed: C12.1, R22.1, R23.2
unnamed: C13.2, C14.2, R24.2, U13.5
unnamed: C14.1, R25.2, U12.3 (+)
unnamed: CA15.1, RA30.1, RB31.1, U7.3 (+)
unnamed: CA15.2, RA30.2, U6.1 (A)
unnamed: CA17.1, RA33.1, RB34.1, U7.14 (+)
unnamed: CA17.2, RA33.2, U8.1 (A)
unnamed: CA19.1, RA36.1, RB37.1, U10.3 (+)
unnamed: CA19.2, RA36.2, U9.1 (A)
unnamed: CA21.1, RA39.1, RB40.1, U10.14 (+)
unnamed: CA21.2, RA39.2, U11.1 (A)
unnamed: CB16.2, U6.5 (+), U7.5
unnamed: CB18.2, U7.12, U8.5 (+)
unnamed: CB20.2, U9.5 (+), U10.5
unnamed: CB22.2, U10.12, U11.5 (+)
unnamed: D1.1 (K), D4.2 (A), J8.1
unnamed: D2.1 (K), D3.2 (A), J8.2
unnamed: D5.1 (K), D6.2 (A), RV_PITCH_BEND1.2
unnamed: J9.1, R27.2, R28.1
unnamed: J9.2, R28.2, R29.1
unnamed: Q1.2 (B), R11.1
unnamed: Q2.2 (B), R16.2
unnamed: Q2.3 (C), Q3.1 (B), U2.6
unnamed: Q3.3 (E), R16.1, R17.2
unnamed: Q4.1 (B), U1.10 (Vout)
unnamed: R9.1, R10.2, U4.3 (+), U4.5 (+), U5.3 (+), U5.5 (+)
unnamed: R13.2, RV1.3
unnamed: R14.1, RV1.1
unnamed: R15.1, R18.2, U2.2 (-)
unnamed: R21.2, U13.4 (-)
unnamed: R22.2, U13.1
unnamed: R26.1, U13.2 (DIODE_BIAS)
unnamed: R27.1, U12.2 (-), U12.6
unnamed: R42.1, U3.2 (VI)
unnamed: RC32.2, U7.1
unnamed: RC35.2, U7.16
unnamed: RC38.2, U10.1
unnamed: RC41.2, U10.16
unnamed: U2.7 (V+), ZD1.2 (A)

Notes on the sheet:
Expander to extra 4 voice
MAIN VOLUME
On panel
